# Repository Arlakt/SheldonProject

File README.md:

# Sheldon Project
Sheldon project makes a [Parrot A.R. Drone 2.0](http://ardrone2.parrot.com/) follow a beacon.  
It takes place within the [Critical Embedded Systems course](http://gei.insa-toulouse.fr/fr/formation_initiale/drones.html) at [INSA Toulouse](http://www.insa-toulouse.fr/) engineering school.

Website: https://sites.google.com/site/projetsecinsa/projets-2015-2016/projct-sheldon

The project features:
- Embedded software to be run on the drone
- Embedded board and sensors to receive the beacon's signal
- The beacon, a device emitting ultrasonic waves

## How to use the embedded software
1. Install the GNU C compiler for ARM: gcc-arm-linux-gnueabi  
Packages are available for most Linux distributions
2. Build the "CDC-ACM" kernel module and upload it to the drone  
see https://sites.google.com/site/projetsecinsa/documents-techniques/outils-et-methodes/cross-compiler-pour
3. Make sure that a `/dev/ttyACM*` device is created when you plug the receiver board
4. Clone the repository and build the program:
```
git clone https://github.com/Arlakt/SheldonProject.git
cd SheldonProject/embedded-sw/
make
```
5. Upload it to the drone and start a telnet session to run the program:
`./upload.sh`
```
# insmod /data/video/modules/cdc-acm.ko
# chmod +x /data/video/main.elf
# /data/video/main.elf
```

## Authors
[Yorrick Barnay](https://github.com/Elskou), [Julien Cassette](https://github.com/jcassette), [Raphaël Roy](https://github.com/raphael-roy), [Romain Taprest](https://github.com/Arlakt)

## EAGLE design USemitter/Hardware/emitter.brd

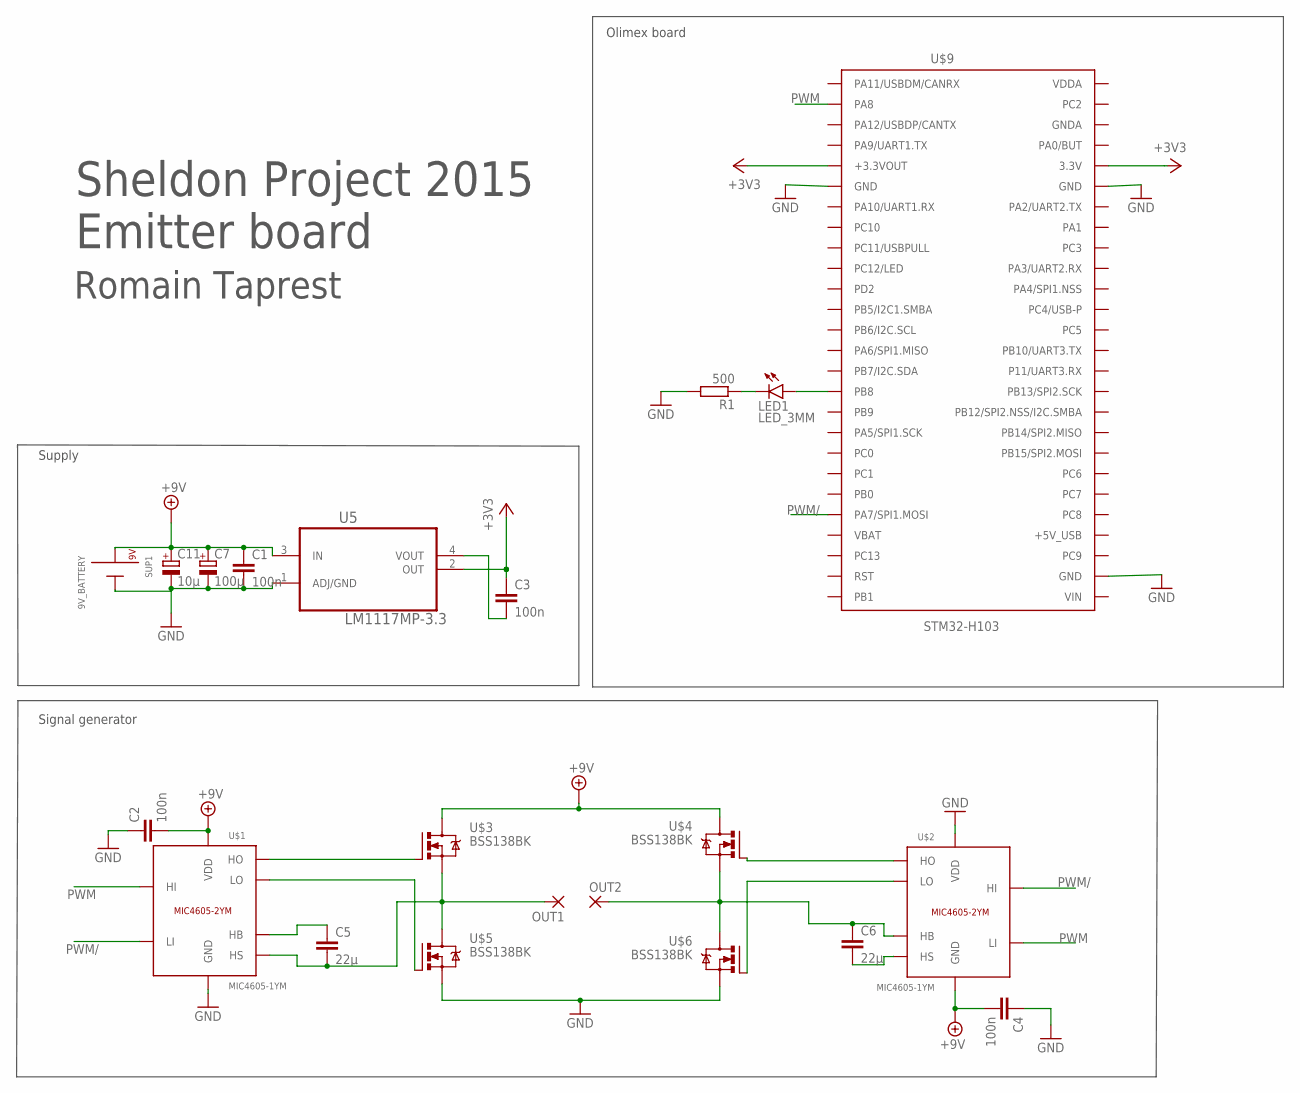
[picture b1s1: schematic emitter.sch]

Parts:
C1, C2, C3, C4: 100n; C050-025X075
C5, C6: 22µ; C050-025X075
C7: 100µ; E2,5-6
C11: 10µ; E2,5-6
LED1: LED_3MM; LED3MM
OUT1, OUT2: 2,54/1,0
R1: 500; 0207/10
SUP1: 9V_BATTERY
U5: LM1117MP-3.3; SOT230P696X180-4N
U$1, U$2: MIC4605-1YM; SOIC08
U$3, U$4, U$5, U$6: BSS138BK; SOT23
U$9: STM32-H103

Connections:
+3V3: C3.1, U5.2 (OUT), U$9.3.3V, U$9.+3.3VOUT
+9V: C1.1, C2.2, C4.2, C7.+, C11.+, SUP1.P$1 (9V), U5.3 (IN), U$1.1 (VDD), U$2.7 (GND), U$3.3 (D), U$4.3 (D)
GND: C1.2, C2.1, C4.1, C7.-, C11.-, R1.2, SUP1.P$2 (GND), U5.1 (ADJ/GND), U$1.7 (GND), U$2.1 (VDD), U$5.2 (S), U$6.2 (S), U$9.GND@1 (GND), U$9.GND@2 (GND), U$9.GND@3 (GND)
unnamed: C3.2, U5.4 (VOUT)
unnamed: LED1.K (C), R1.1
unnamed: U$1.3 (HO), U$3.1 (G)
unnamed: U$1.8 (LO), U$5.1 (G)
unnamed: U$2.3 (HO), U$4.1 (G)
unnamed: U$2.8 (LO), U$6.1 (G)
unnamed: C5.1, U$1.2 (HB)
unnamed: C6.2, U$2.4 (HS)
unnamed: LED1.A, U$9.PB8
OUT1: C5.2, OUT1.1, U$1.4 (HS), U$3.2 (S), U$5.3 (D)
OUT2: C6.1, OUT2.1, U$2.2 (HB), U$4.2 (S), U$6.3 (D)
PWM: U$1.5 (HI), U$2.6 (LI), U$9.PA8
PWM/: U$1.6 (LI), U$2.5 (HI), U$9.PA7/SPI1.MOSI

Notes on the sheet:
Sheldon Project 2015 Emitter board
Supply
Olimex board
Signal generator
Romain Taprest

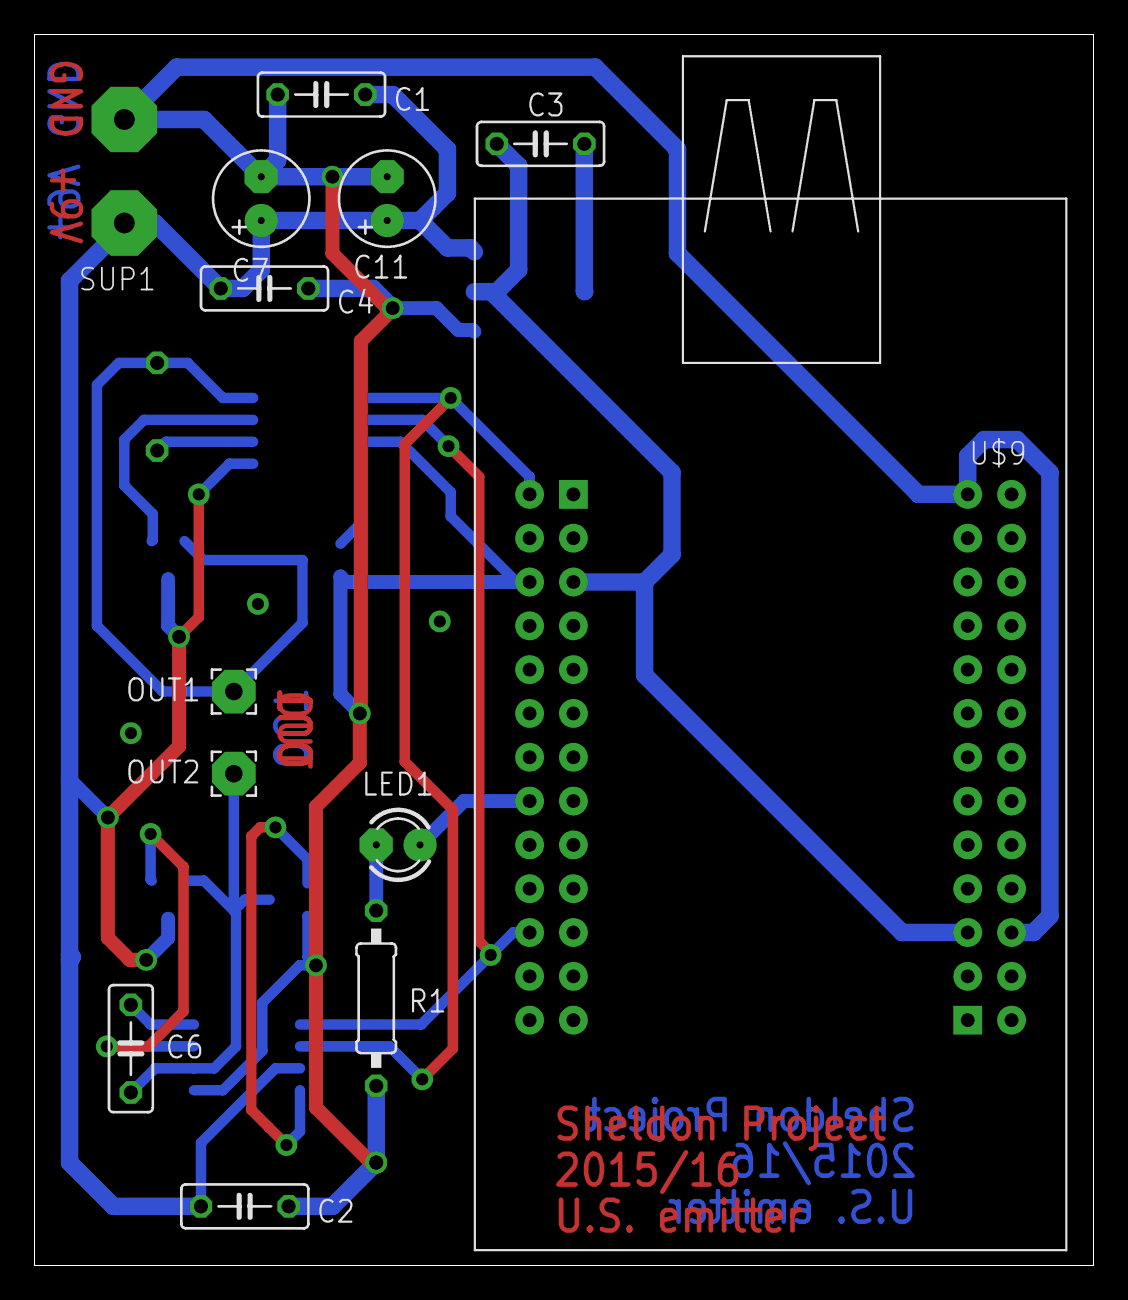
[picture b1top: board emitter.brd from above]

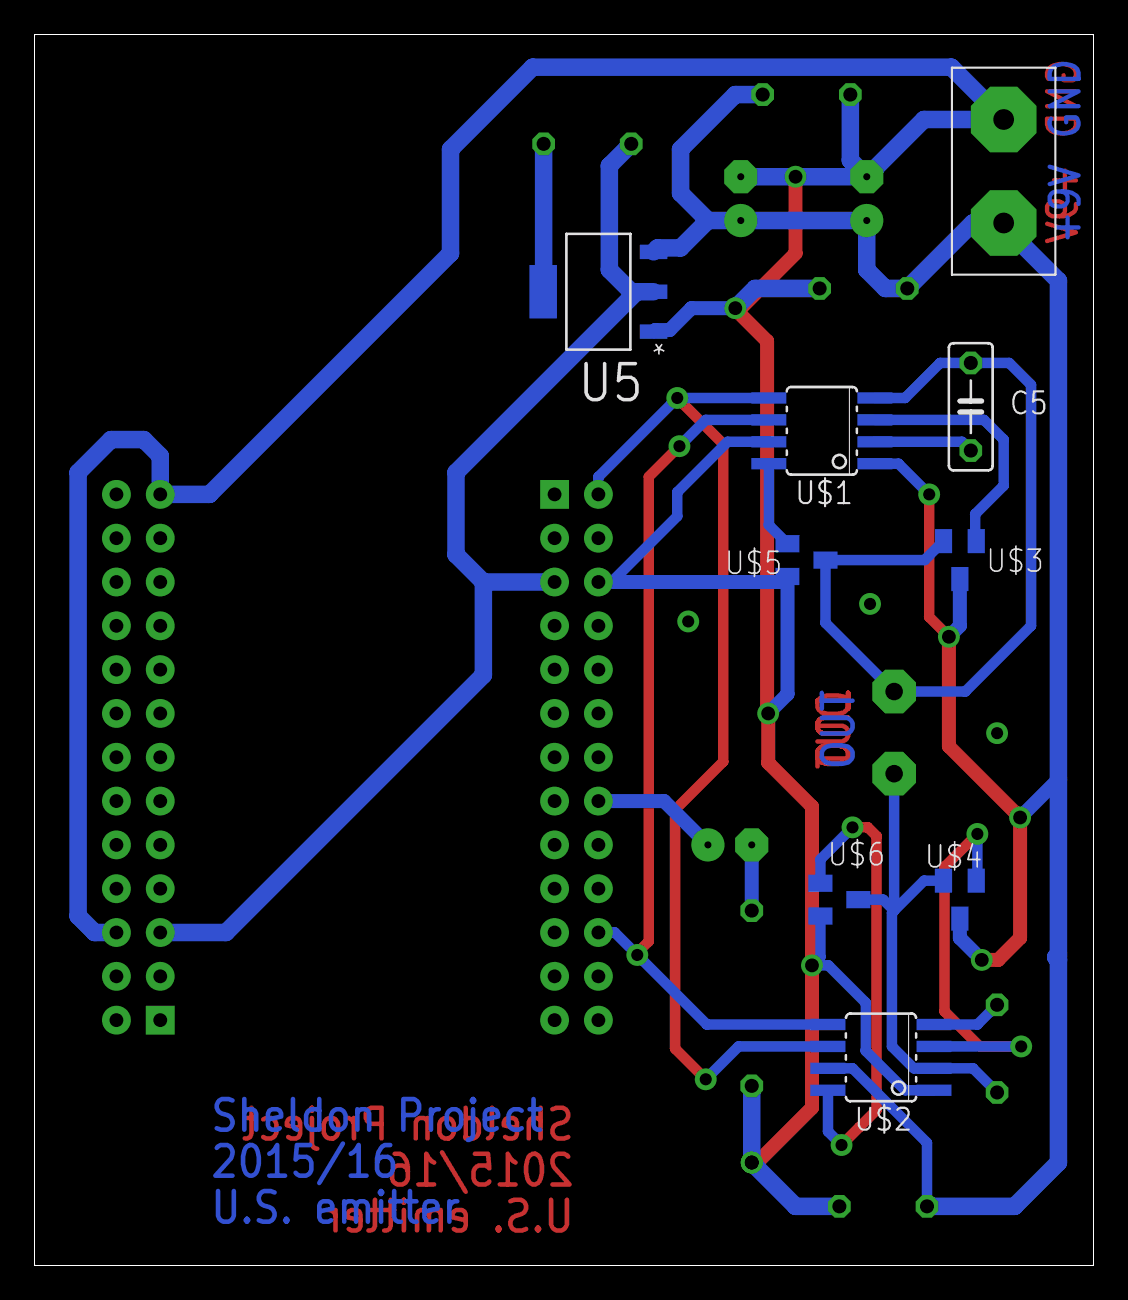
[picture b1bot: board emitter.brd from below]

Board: 2 copper layers, 61.4 x 71.4 mm, 21 parts (9 on the bottom side), 16 nets.

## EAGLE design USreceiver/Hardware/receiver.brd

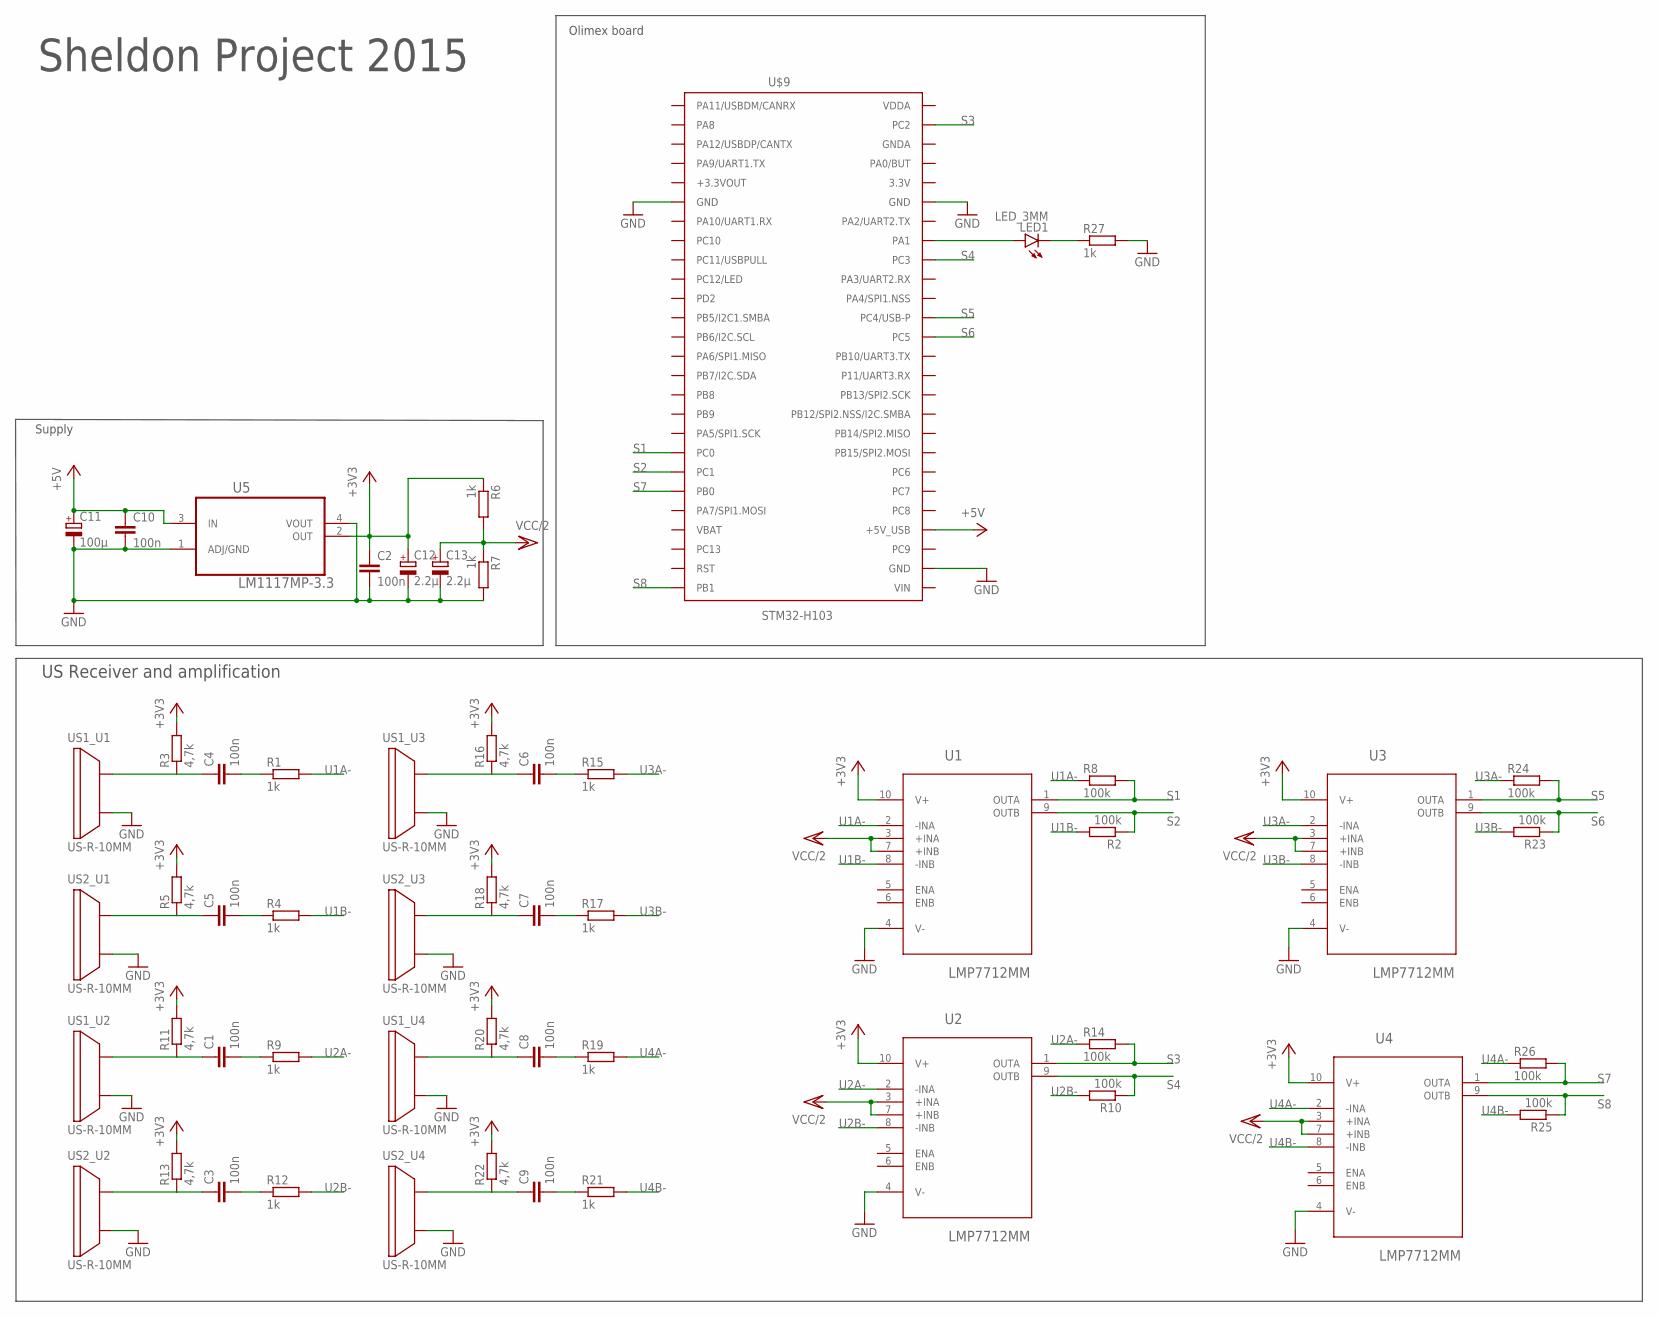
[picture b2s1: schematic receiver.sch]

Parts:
C1, C2, C3, C4, C5, C6, C7, C8, C9, C10: 100n; C0603
C11: 100µ; E2,5-6
C12, C13: 2.2µ; E2,5-6
LED1: LED_3MM; LED3MM
R1, R4, R6, R7, R9, R12, R15, R17, R19, R21, R27: 1k; R0603
R2, R8, R10, R14, R23, R24, R25, R26: 100k; R0603
R3, R5, R11, R13, R16, R18, R20, R22: 4,7k; R0603
U1, U2, U3, U4: LMP7712MM; SOP50P490X110-10N
U5: LM1117MP-3.3; SOT230P696X180-4N
U$9: STM32-H103
US1_U1, US1_U2, US1_U3, US1_U4, US2_U1, US2_U2, US2_U3, US2_U4: US-R-10MM

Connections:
+3V3: C2.1, C12.+, R3.2, R5.2, R6.1, R11.2, R13.2, R16.2, R18.2, R20.2, R22.2, U1.10 (V+), U2.10 (V+), U3.10 (V+), U4.10 (V+), U5.2 (OUT)
+5V: C10.1, C11.+, U5.3 (IN), U$9.+5V_USB
GND: C2.2, C10.2, C11.-, C12.-, C13.-, R7.2, R27.2, U1.4 (V-), U2.4 (V-), U3.4 (V-), U4.4 (V-), U5.1 (ADJ/GND), U5.4 (VOUT), U$9.GND@1 (GND), U$9.GND@2 (GND), U$9.GND@3 (GND), US1_U1.P$2, US1_U2.P$2, US1_U3.P$2, US1_U4.P$2, US2_U1.P$2, US2_U2.P$2, US2_U3.P$2, US2_U4.P$2
unnamed: C1.1, R11.1, US1_U2.P$1
unnamed: C1.2, R9.1
unnamed: C4.1, R3.1, US1_U1.P$1
unnamed: C4.2, R1.1
unnamed: C5.1, R5.1, US2_U1.P$1
unnamed: C5.2, R4.1
unnamed: C3.1, R13.1, US2_U2.P$1
unnamed: C3.2, R12.1
unnamed: C6.1, R16.1, US1_U3.P$1
unnamed: C6.2, R15.1
unnamed: C7.1, R18.1, US2_U3.P$1
unnamed: C7.2, R17.1
unnamed: C8.1, R20.1, US1_U4.P$1
unnamed: C8.2, R19.1
unnamed: C9.1, R22.1, US2_U4.P$1
unnamed: C9.2, R21.1
unnamed: LED1.A, U$9.PA1
unnamed: LED1.K (C), R27.1
S1: R8.2, U1.1 (OUTA), U$9.PC0
S2: R2.1, U1.9 (OUTB), U$9.PC1
S3: R14.2, U2.1 (OUTA), U$9.PC2
S4: R10.1, U2.9 (OUTB), U$9.PC3
S5: R24.2, U3.1 (OUTA), U$9.PC4/USB-P
S6: R23.1, U3.9 (OUTB), U$9.PC5
S7: R26.2, U4.1 (OUTA), U$9.PB0
S8: R25.1, U4.9 (OUTB), U$9.PB1
U1A-: R1.2, R8.1, U1.2 (-INA)
U1B-: R2.2, R4.2, U1.8 (-INB)
U2A-: R9.2, R14.1, U2.2 (-INA)
U2B-: R10.2, R12.2, U2.8 (-INB)
U3A-: R15.2, R24.1, U3.2 (-INA)
U3B-: R17.2, R23.2, U3.8 (-INB)
U4A-: R19.2, R26.1, U4.2 (-INA)
U4B-: R21.2, R25.2, U4.8 (-INB)
VCC/2: C13.+, R6.2, R7.1, U1.3 (+INA), U1.7 (+INB), U2.3 (+INA), U2.7 (+INB), U3.3 (+INA), U3.7 (+INB), U4.3 (+INA), U4.7 (+INB)

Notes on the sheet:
US Receiver and amplification
Sheldon Project 2015
Supply
Olimex board

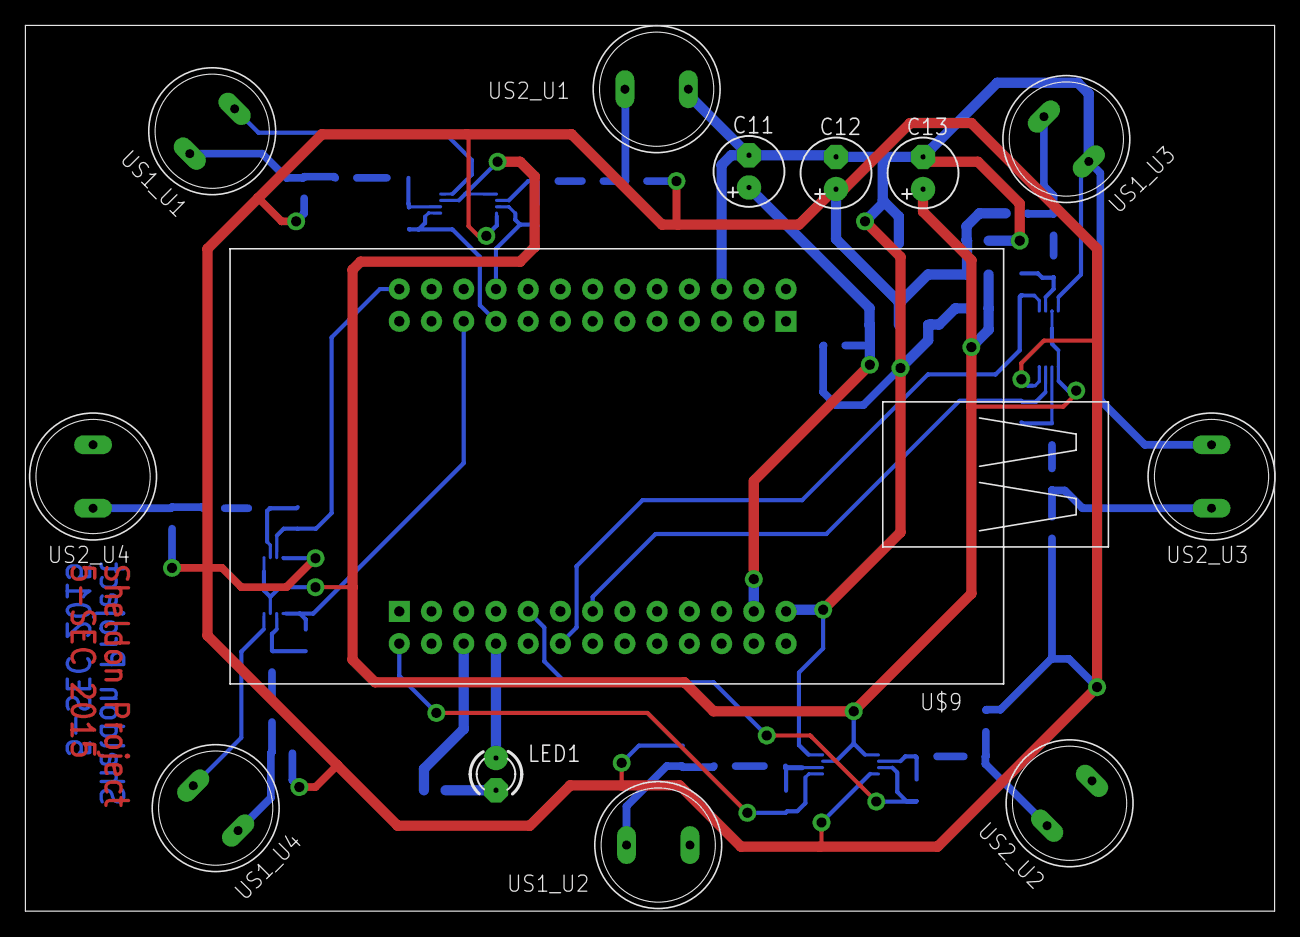
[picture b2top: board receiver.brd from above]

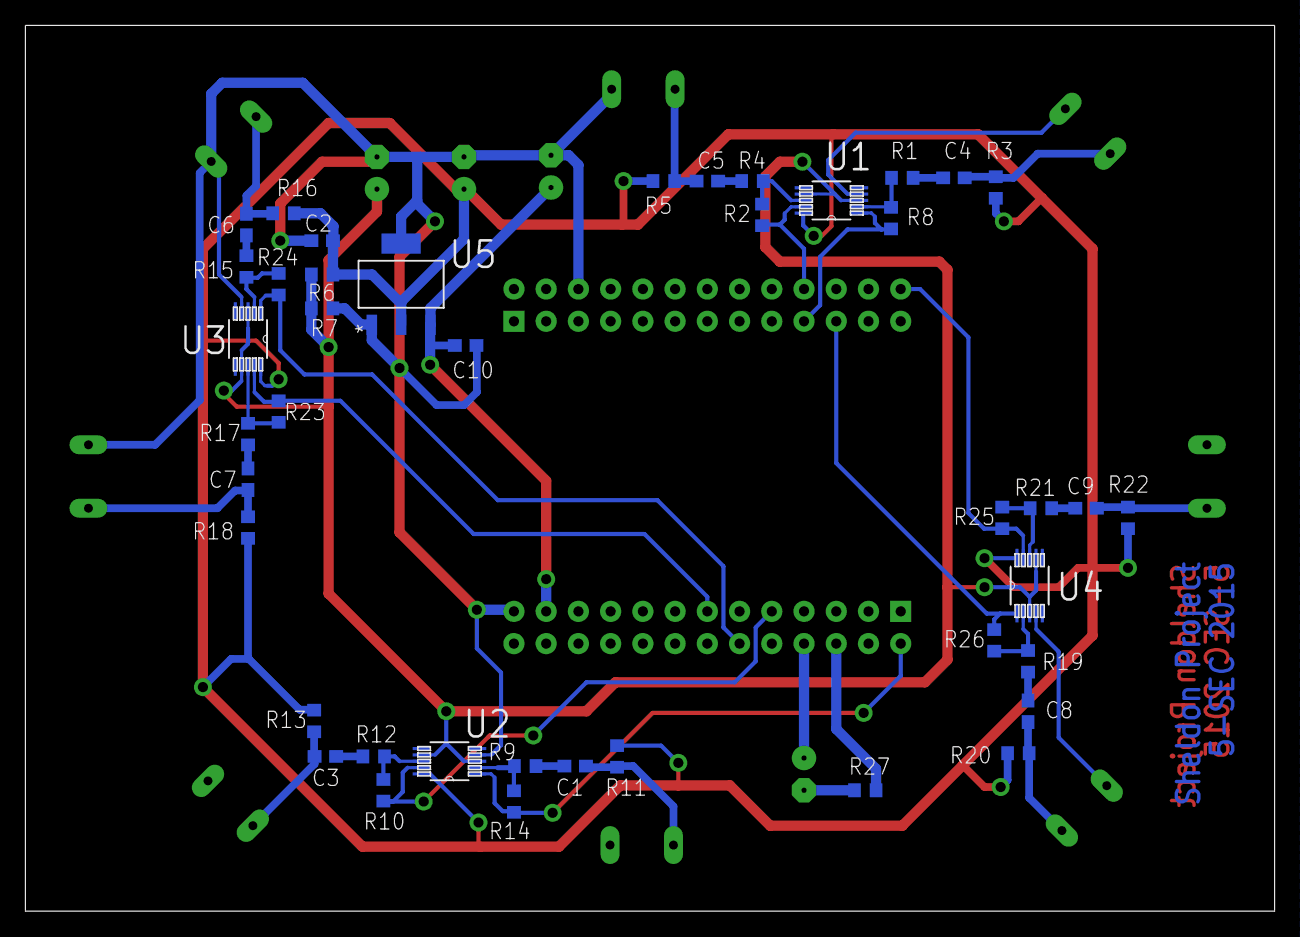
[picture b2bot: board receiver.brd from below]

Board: 2 copper layers, 98.4 x 69.8 mm, 55 parts (42 on the bottom side), 38 nets.

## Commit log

2015-10-23 Update README.md
    Add website address
2015-11-03 Creation of files and our own library
2015-11-03 Added eagle temp files to ignore
2015-11-07 Revert "Creation of files and our own library"
    This reverts commit 7f03c46b7e32d44c8612b50bc91e36f665de45a0.
2015-11-07 Revert "Revert "Creation of files and our own library""
    This reverts commit aa77fd2934e99a6e813e5d8c6b386274c490f614.
2015-11-07 Added a new Amplifier
2015-11-07 Schematic done. Board started. Library updated.
2015-11-08 Board finished
    Board design is finished, pictures are exported. Ready to be sent in
    fab.
2015-11-09 Creation of the STM32 software thanks to STM32Cube
    Ready for a test with JTAG on Olimex STM32-H103
    USB com still needs to be configured/started
2015-11-09 Added Fab guide + finished test program
    The program should open a COM port and send bytes repetedly. DMA should
    also start.
2015-11-13 Changed LMP7712 pad width because it was impossible to print the board
2015-11-13 First camera test program
2015-11-16 Added Demo with Arduino and Processing
2015-11-19 Added UML description for communication between PC and receiver board.
2015-11-19 Error of merging video branch
2015-11-19 Adedd example serial program
2015-11-20 Added write check
2015-11-20 Support for host and drone compilation targets
2015-11-20 First commit for navigation strategy
2015-11-20 Update .gitignore for hidden and backup files
2015-11-20 Organizing the navigation_strategy basis files
2015-11-20 Organizing the navigation_strategy basis files - Missing files added
2015-11-20 Use non blocking mode for the drone
2015-11-21 Small changes according to forums
2015-11-26 Fully changed Olimex program. Now serial over USB is working.
    Program made with CubeMX did not work at all. This whole new project is
    made from a drone project from last year. A lot of code is useless in
    our case, but the serial communication over USB is finally working. Next
    step is to remove useless code and add our own code for reading analog
    inputs and send them.
2015-11-26 Maj serial.c
2015-11-26 Most parts of the program cleaned. Advanced serial function written : everything is ready to send signal strengths in frames.
2015-11-26 Modified serial program with init and start functions and added data parsing.
2015-11-26 ADC Seems to be fully operationnal, data are now ready to be processed before sending.
    ADC is sampling each signal at 100kHz thanks to Timer1
    (sampleAcquisition.c)
    Each sample is catch and ready to be sent to a function for processing.
    A handler is ready to send data to the PC at a specific frequency thanks
    to Timer2 (usbComm.c)
2015-11-26 Program complete. To be tested on board.
    Program is sampling each signal at 100kHz, and sending signals strength
    at 1Hz on 16 bits.
2015-11-27 Fixed a little problem with the index to know which signal is being converted (removed from reset function).
2015-11-27 Use exit, check the device is a serial port
2015-11-27 Added debug macro
2015-11-27 New parser
2015-11-27 Serial options
2015-11-27 Fixed some bugs on signal processing, but noticed a BIG mistake to resolve ==> DMA is mandatory with ADC scan mode.
    DMA procedures must entirely replace the EOC procedure.... A lot of work
    to do.
2015-11-27 Everything's working ! ADC data are now managed with DMA.
    Next problem to solve : strengths are not stable over time.
2015-11-29 Added program design diagram.
2015-11-30 Added files and function to compute angle and position thanks to signals strength.
2015-11-30 Remove call to serial_start
2015-11-30 Modified parser
2015-11-30 Converted serial.c to a library and an example program
2015-11-30 Move tty check to serial_init
2015-11-30 Move files from serial-example directory
2015-11-30 Changed the order of MSB and LSB
2015-11-30 Rassemblement des fichiers .h
2015-11-30 Suppression de API_movement
2015-11-30 Reoranisation du dossier
2015-11-30 Liens cassés - Réparation
2015-11-30 Fichier de test de calcul position
2015-11-30 Calcul de l'angle et distance de la balise
2015-11-30 Thread added
2015-11-30 Thread added side effect
2015-11-30 Thread added sideeffect
2015-11-30 Useful for uploading and launching program on drone
2015-11-30 Cleaning files
2015-12-01 Clean makefile
2015-12-01 Declaration of extern variables moved in the .h
2015-12-01 Declaration of extern variables moved in the .h common.h fully moved in at_commands_builder.h
2015-12-01 New makefile Makes test_position && test_movement at the same time
2015-12-09 rajout possibilité attente ou non
2015-12-09 reflexion concernant complex_position
2015-12-09 modif des test
2015-12-09 rename thread
2015-12-11 Added emitter programm for STM32F103RB
2015-12-11 Computed strengths are changed in function of emitter duty cycle. Measures frequency is increased to 5 Hz.
2015-12-11 Fix C flags
2015-12-12 Ajout de #ifndef et #define
2015-12-12 Code fonctionnel
2015-12-12 Ajout de #ifndef et #define + code fonctionnel
2015-12-12 Probleme compilation unistd résolu
2015-12-12 New threshold
2015-12-12 Add threshold and use it
2015-12-12 Prevent drone from moving to test
2015-12-12 Useful to build and run
2015-12-14 Added Makefile for Windows (with cygwin)
2015-12-14 Added function to get the real angle and position
2015-12-15 Updated angle algorithm and script for uploading
2015-12-17 Ctrl -c to make the drone land
2015-12-17 Add ctrl-c feature
2016-01-04 Makefiles and upload script for Windows updated
2016-01-04 Remove executable file flag and move headers to inc directory
2016-01-04 Remove executable file flag
2016-01-04 Changes to do simple tests with rotation, with et scanf on terminal
2016-01-04 Automated Scripts updated
2016-01-04 Makefile updated
2016-01-04 Rename test_pos.c to main.c
2016-01-04 Change include paths and fix extern variables
2016-01-04 Fix pos incorrectly declared
2016-01-04 Add Makefile
2016-01-04 Fixed makefile issue when linking Cleaned source code from useless comments, and some other things.
2016-01-04 Fixed rotation powers values. Removed some warnings.
2016-01-04 Just adding a printf to see position
2016-01-04 Added CTRL+C manager to correctly exit the program with a landing. => works well !
2016-01-05 Conclusive tests for angle tracking. I added a new method to compute distance, et added the distance tracking algorithm, but to be tested.
2016-01-07 Adding management of the situation where no signal is detected
2016-01-08 - Add a step for the drone to go up just after taking off (but not really working...) - The drone does not try to keep a constant distance, it just moves forward to the emitter
2016-01-09 Add Maximum Detection for the US receiver
    The program for the olimex and its associated Processing program
2016-01-11 Add upload script
2016-01-11 Update Makefile and upload script
2016-01-11 Remove old files
2016-01-14 Fix upload.sh to force binary transfer, and to allow to upload any file
2016-01-14 First draft
2016-01-14 Add define to change destion ip/port of navdata
2016-01-14 First draft of altitude thread
2016-01-14 Fix missing include stdint.h
2016-01-14 Creation of emitter hardware files
2016-01-14 - Emitter schematic almost finished. - STM32 code generator modified to integrate the LED and the reversed PWM. ==> Code must still be generated
2016-01-15 Eagle files for the emitter board finished (designed and routed). To be verified and produce if OK.
2016-01-17 indentation
2016-01-17 Improve navdata_recv
2016-01-17 Navdata example program: send AT config command, etc...
2016-01-18 Create licence
2016-01-18 Rename licence to LICENCE
2016-01-18 Add data parsing in navdata_get
2016-01-18 Fix parsing in navdata_get
2016-01-18 Cleaning "seq number"
2016-01-19 Add navdata_print
2016-01-19 Altitude thread
2016-01-19 Modify navdata test program
2016-01-19 Fix header guards
2016-01-19 Integrate altitude thread - Add mutex for AT commands (socket and sequence number) - Modify track_position to use AT mutex - Start altitude thread from main - Add objs in makefile
2016-01-19 Improve Makefile
2016-01-19 Lock AT command mutex in main
2016-01-19 Add AT_CTRL command
2016-01-19 Modify altitude thread -> Altitude navdata working
2016-01-21 Final version of the emitter board
2016-01-24 Updating emitter board program for the new board.
2016-01-25 Try altitude correction
